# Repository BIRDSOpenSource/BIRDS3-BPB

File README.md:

<p align="center">
<a href="https://lean-sat.org/opensource/" class="button icon calendar">Join Monthly Webinar</a>
</p>

<div align="center">

</div>

# BIRDS3-BPB
The two different designs of the BPB used in the BIRDS3 mission, one with CPLD and one without.

## About the BIRDS3 Program:

The project was led by Kyushu Institute of Technology in Japan and involves students from Sri Lanka, Bhutan, Nepal and Japan.
Satellite Names: NepaliSat-1 (Nepal), Raavana-1 (Sri Lanka) and Ugiusu (Japan)

Stakeholders: Nepal Academy of Science and Technology (NAST) for Nepal, Arthur C Clarke Institute for Modern Technologies (ACCIMT) for Sri Lanka, and Kyushu Institute of Technology (Kyutech) for Japan.

Project duration: 2018-2020

CubeSat: 1U (10x10x10) cm3

Weight: 1.13kg

Launch Date: 17th April 2019

BIRDS-3 has 4 main missions in total; LoRa Demonstration Mission (LDM), Imaging Mission (CAM), Attitude Determination and Control Mission (ADCS) and Software Configurable Backplane Mission (BPB) 

## Organisation structure

## Features

## I like this project, can I help you?
You are welcome 🙂

* Give us a star ⭐
* Watch repository to be notified about updates 👀
* If you will find some errors, report them in Issues 🐞
* Try Birds designs on some real computer and let us know how it worked in Discussions. 💬
* We would greatly appreciate if you would also tell others about this ecosystem, it helps us to improve BIRDS Open Source. Thank you!

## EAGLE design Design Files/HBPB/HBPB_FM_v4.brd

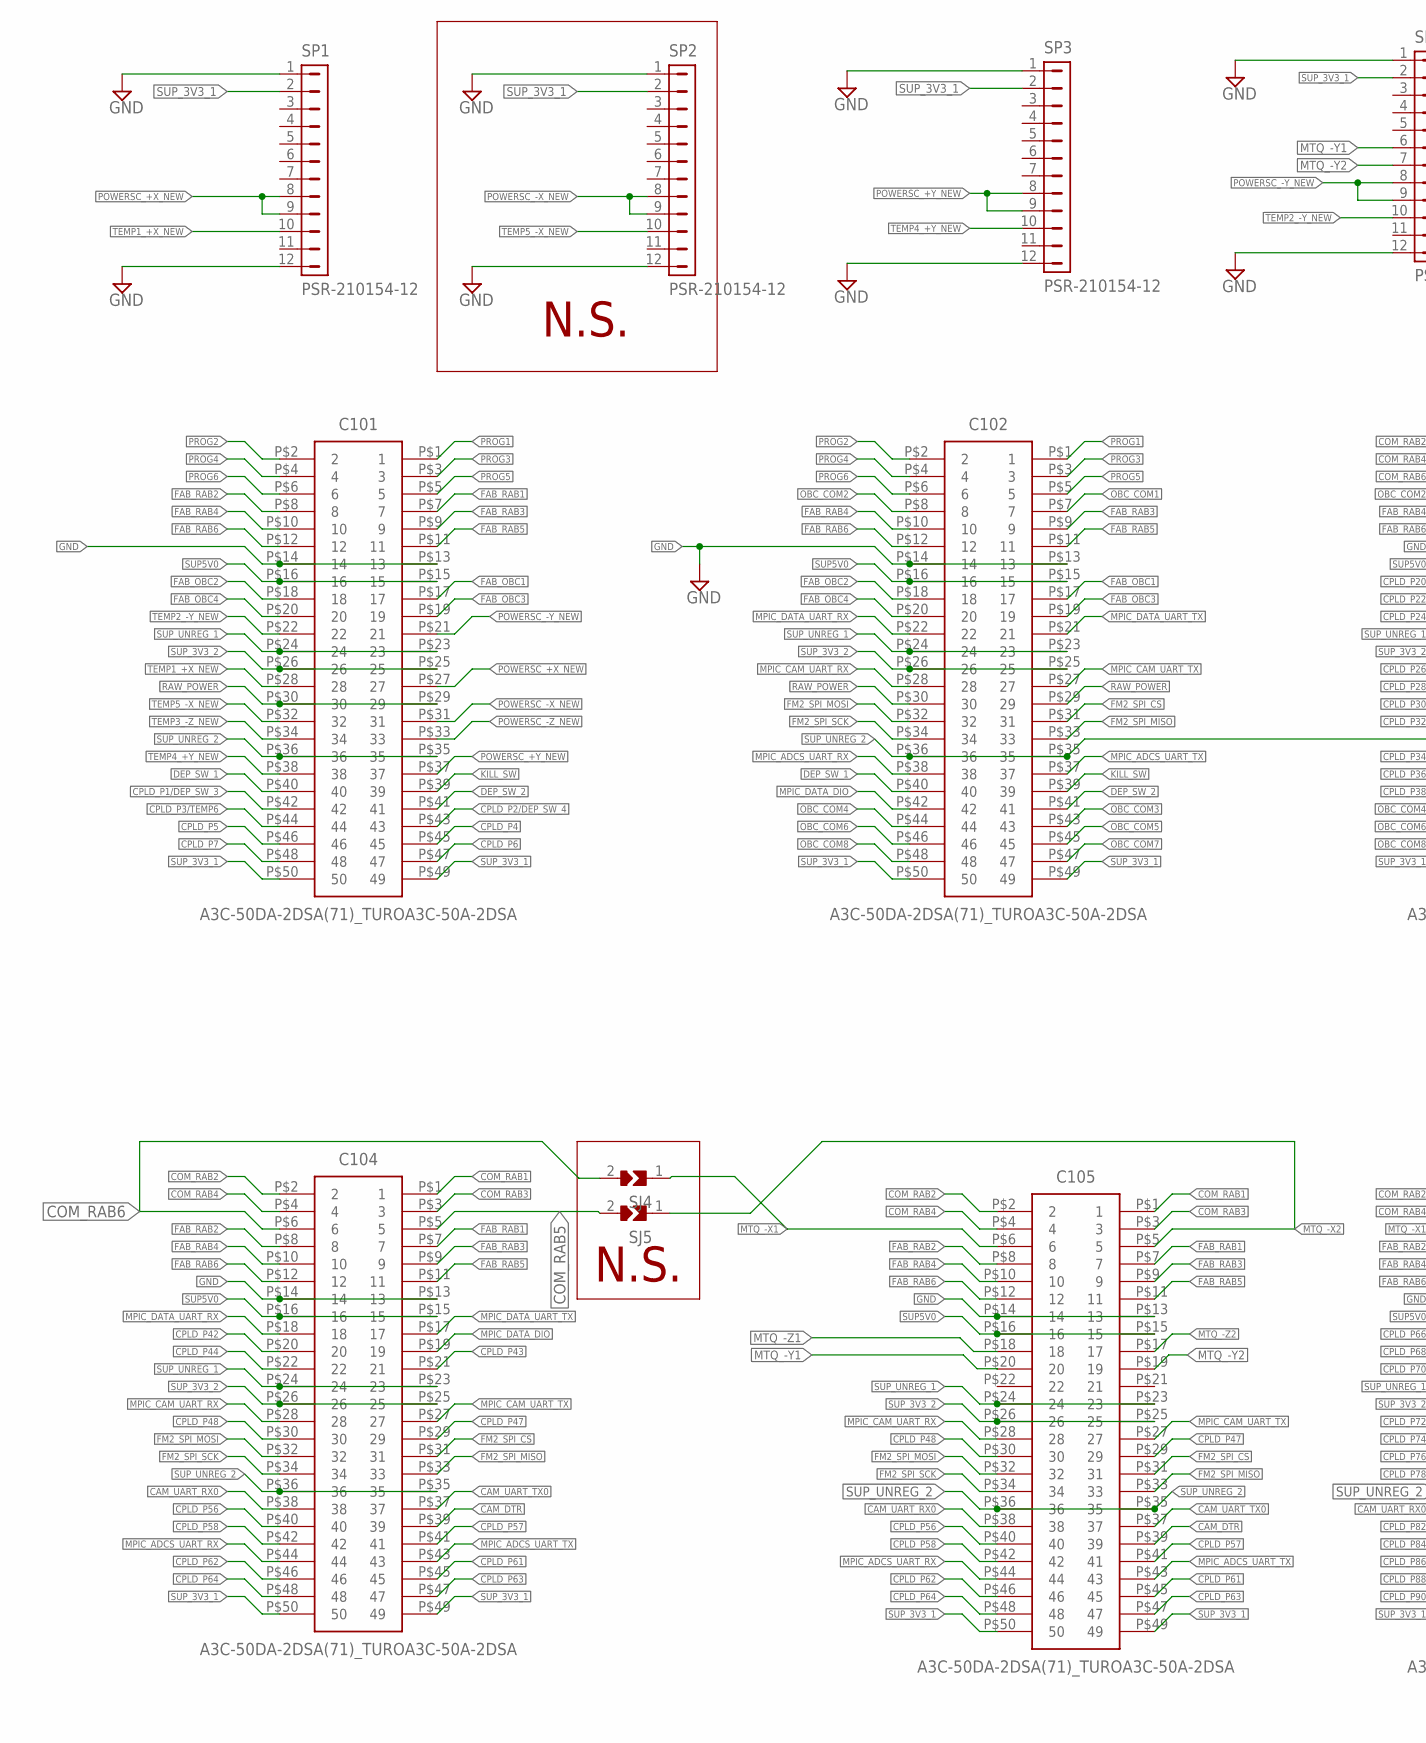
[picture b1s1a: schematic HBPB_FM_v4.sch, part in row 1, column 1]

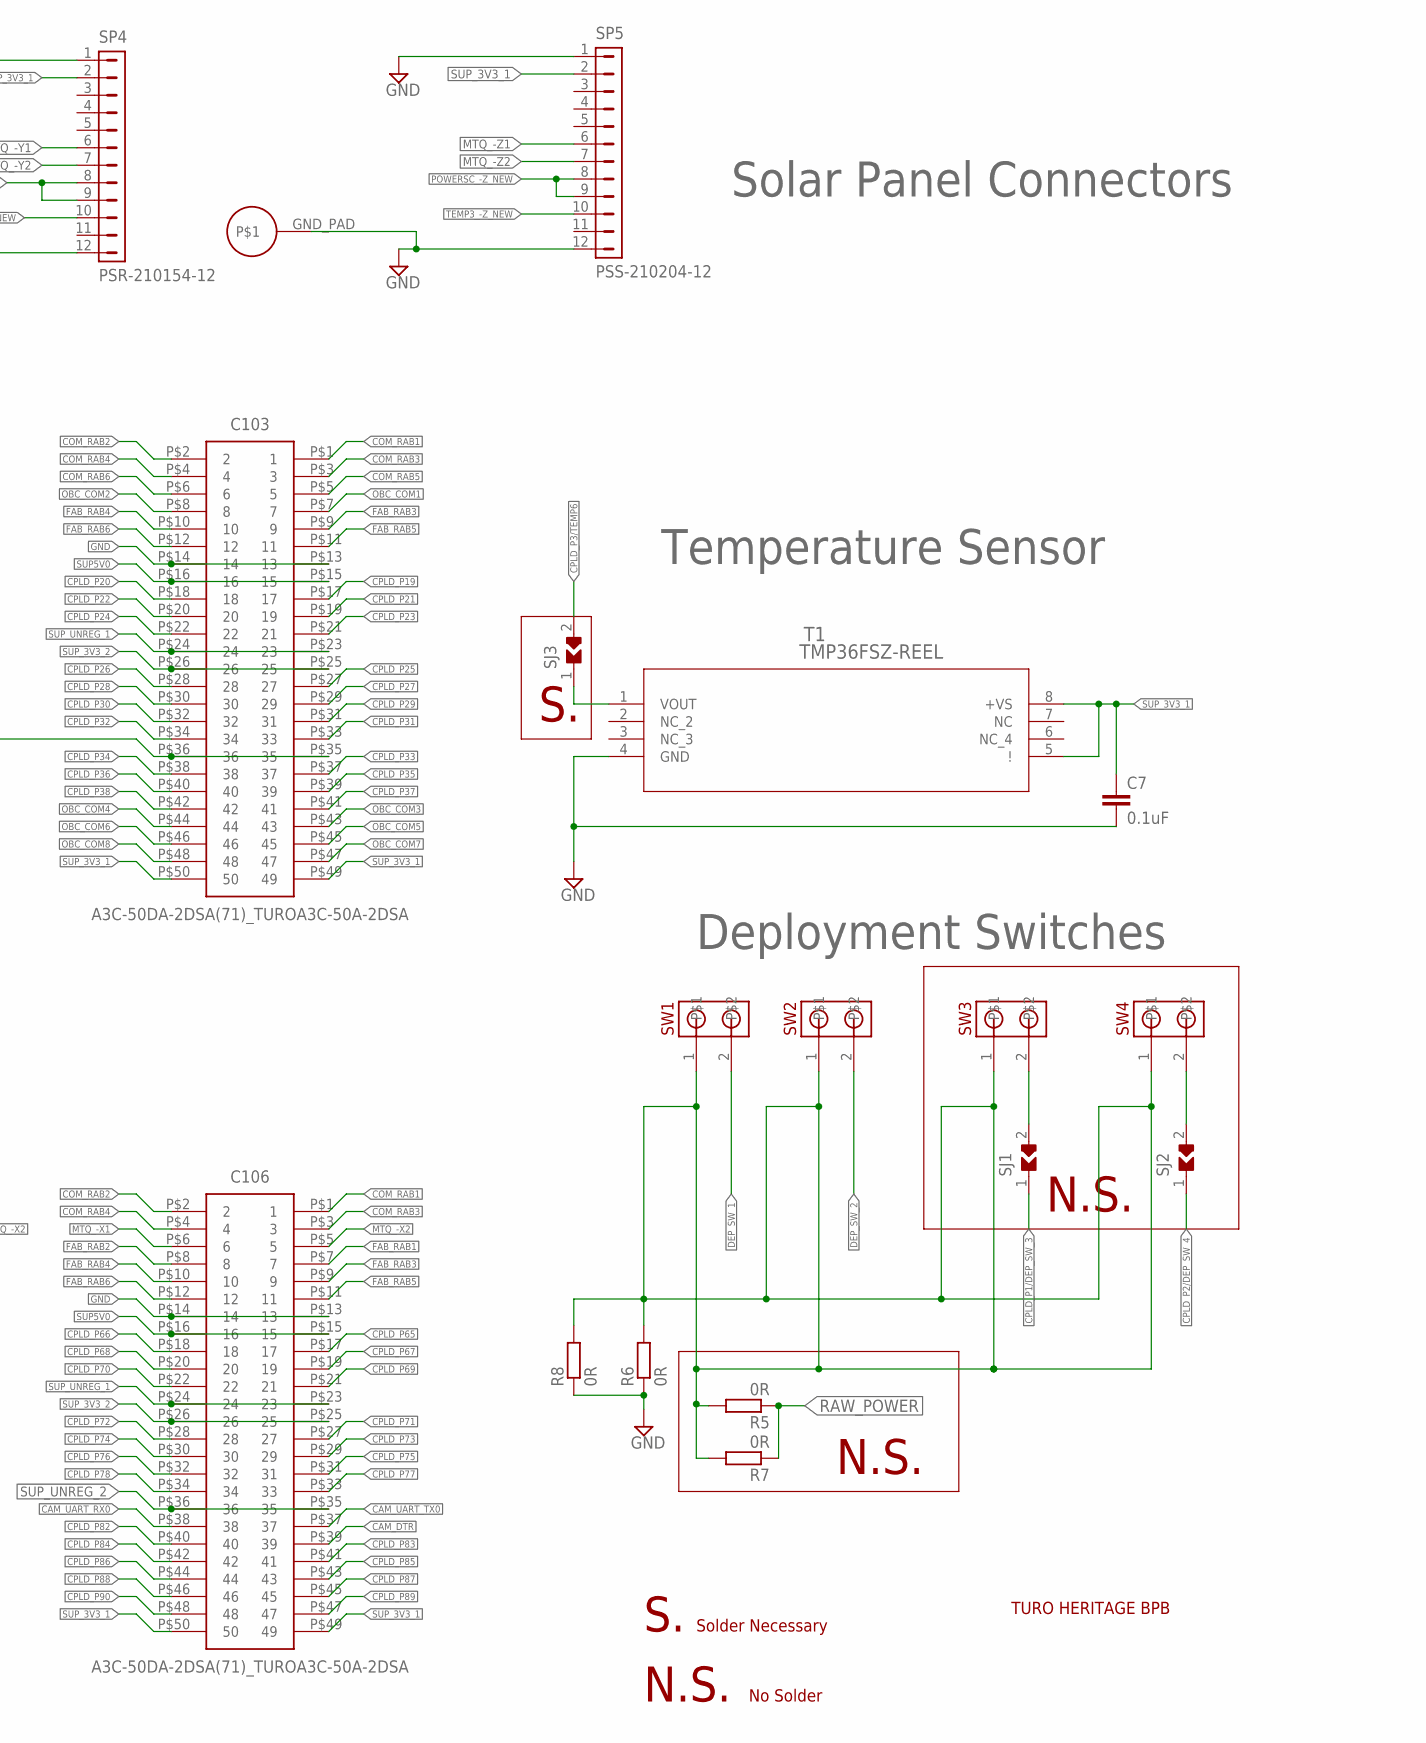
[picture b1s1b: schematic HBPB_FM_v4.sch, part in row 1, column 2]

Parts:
C7: 0.1uF; C0402
C101, C102, C103, C104, C105, C106: A3C-50DA-2DSA(71)_TUROA3C-50A-2DSA; SHDR50W60P200_2X25_5000X400X44_TR
R5, R6, R7, R8: 0R; R3216
SJ1, SJ3, SJ4, SJ5: SJ_BY_TURO; SJ_TURO
SJ2: 0R; SJ_TURO
SP1, SP2, SP3, SP4: PSR-210154-12; PIN1X12/90
SP5: PSS-210204-12; PIN1X12
SW1, SW2, SW3, SW4: MOLEX-CONN-2-0554600272; MOLEX-CONN-2-BIRDS
T1: TMP36FSZ-REEL; R_8
U$1: GND_PAD

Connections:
CAM_DTR: C104.P$39 (39), C105.P$39 (39), C106.P$39 (39)
CAM_UART_RX0: C104.P$38 (38), C105.P$38 (38), C106.P$38 (38)
CAM_UART_TX0: C104.P$37 (37), C105.P$37 (37), C106.P$37 (37)
COM_RAB1: C103.P$1 (1), C104.P$1 (1), C105.P$1 (1), C106.P$1 (1)
COM_RAB2: C103.P$2 (2), C104.P$2 (2), C105.P$2 (2), C106.P$2 (2)
COM_RAB3: C103.P$3 (3), C104.P$3 (3), C105.P$3 (3), C106.P$3 (3)
COM_RAB4: C103.P$4 (4), C104.P$4 (4), C105.P$4 (4), C106.P$4 (4)
COM_RAB5: C103.P$5 (5), C104.P$5 (5), SJ5.2
COM_RAB6: C103.P$6 (6), C104.P$6 (6), SJ4.2
CPLD_P1/DEP_SW_3: C101.P$42 (42), SJ1.1
CPLD_P2/DEP_SW_4: C101.P$43 (43), SJ2.1
CPLD_P3/TEMP6: C101.P$44 (44), SJ3.2
CPLD_P4: C101.P$45 (45)
CPLD_P5: C101.P$46 (46)
CPLD_P6: C101.P$47 (47)
CPLD_P7: C101.P$48 (48)
CPLD_P19: C103.P$17 (17)
CPLD_P20: C103.P$18 (18)
CPLD_P21: C103.P$19 (19)
CPLD_P22: C103.P$20 (20)
CPLD_P23: C103.P$21 (21)
CPLD_P24: C103.P$22 (22)
CPLD_P25: C103.P$27 (27)
CPLD_P26: C103.P$28 (28)
CPLD_P27: C103.P$29 (29)
CPLD_P28: C103.P$30 (30)
CPLD_P29: C103.P$31 (31)
CPLD_P30: C103.P$32 (32)
CPLD_P31: C103.P$33 (33)
CPLD_P32: C103.P$34 (34)
CPLD_P33: C103.P$37 (37)
CPLD_P34: C103.P$38 (38)
CPLD_P35: C103.P$39 (39)
CPLD_P36: C103.P$40 (40)
CPLD_P37: C103.P$41 (41)
CPLD_P38: C103.P$42 (42)
CPLD_P42: C104.P$20 (20)
CPLD_P43: C104.P$21 (21)
CPLD_P44: C104.P$22 (22)
CPLD_P47: C104.P$29 (29), C105.P$29 (29)
CPLD_P48: C104.P$30 (30), C105.P$30 (30)
CPLD_P56: C104.P$40 (40), C105.P$40 (40)
CPLD_P57: C104.P$41 (41), C105.P$41 (41)
CPLD_P58: C104.P$42 (42), C105.P$42 (42)
CPLD_P61: C104.P$45 (45), C105.P$45 (45)
CPLD_P62: C104.P$46 (46), C105.P$46 (46)
CPLD_P63: C104.P$47 (47), C105.P$47 (47)
CPLD_P64: C104.P$48 (48), C105.P$48 (48)
CPLD_P65: C106.P$17 (17)
CPLD_P66: C106.P$18 (18)
CPLD_P67: C106.P$19 (19)
CPLD_P68: C106.P$20 (20)
CPLD_P69: C106.P$21 (21)
CPLD_P70: C106.P$22 (22)
CPLD_P71: C106.P$27 (27)
CPLD_P72: C106.P$28 (28)
CPLD_P73: C106.P$29 (29)
CPLD_P74: C106.P$30 (30)
CPLD_P75: C106.P$31 (31)
CPLD_P76: C106.P$32 (32)
CPLD_P77: C106.P$33 (33)
CPLD_P78: C106.P$34 (34)
CPLD_P82: C106.P$40 (40)
CPLD_P83: C106.P$41 (41)
CPLD_P84: C106.P$42 (42)
CPLD_P85: C106.P$43 (43)
CPLD_P86: C106.P$44 (44)
CPLD_P87: C106.P$45 (45)
CPLD_P88: C106.P$46 (46)
CPLD_P89: C106.P$47 (47)
CPLD_P90: C106.P$48 (48)
DEP_SW_1: C101.P$40 (40), C102.P$40 (40), SW1.2
DEP_SW_2: C101.P$41 (41), C102.P$41 (41), SW2.2
DEP_SW_POWER: R5.2, R6.2, R7.2, R8.2, SW1.1, SW2.1, SW3.1, SW4.1
FAB_OBC1: C101.P$17 (17), C102.P$17 (17)
FAB_OBC2: C101.P$18 (18), C102.P$18 (18)
FAB_OBC3: C101.P$19 (19), C102.P$19 (19)
FAB_OBC4: C101.P$20 (20), C102.P$20 (20)
FAB_RAB1: C101.P$7 (7), C104.P$7 (7), C105.P$7 (7), C106.P$7 (7)
FAB_RAB2: C101.P$8 (8), C104.P$8 (8), C105.P$8 (8), C106.P$8 (8)
FAB_RAB3: C101.P$9 (9), C102.P$9 (9), C103.P$9 (9), C104.P$9 (9), C105.P$9 (9), C106.P$9 (9)
FAB_RAB4: C101.P$10 (10), C102.P$10 (10), C103.P$10 (10), C104.P$10 (10), C105.P$10 (10), C106.P$10 (10)
FAB_RAB5: C101.P$11 (11), C102.P$11 (11), C103.P$11 (11), C104.P$11 (11), C105.P$11 (11), C106.P$11 (11)
FAB_RAB6: C101.P$12 (12), C102.P$12 (12), C103.P$12 (12), C104.P$12 (12), C105.P$12 (12), C106.P$12 (12)
FM2_SPI_CS: C102.P$31 (31), C104.P$31 (31), C105.P$31 (31)
FM2_SPI_MISO: C102.P$33 (33), C104.P$33 (33), C105.P$33 (33)
FM2_SPI_MOSI: C102.P$32 (32), C104.P$32 (32), C105.P$32 (32)
FM2_SPI_SCK: C102.P$34 (34), C104.P$34 (34), C105.P$34 (34)
GND: C7.2, C101.P$13 (13), C101.P$14 (14), C102.P$13 (13), C102.P$14 (14), C103.P$13 (13), C103.P$14 (14), C104.P$13 (13), C104.P$14 (14), C105.P$13 (13), C105.P$14 (14), C106.P$13 (13), C106.P$14 (14), R6.1, R8.1, SP1.1, SP1.12, SP2.1, SP2.12, SP3.1, SP3.12, SP4.1, SP4.12, SP5.1, SP5.12, T1.4 (GND), U$1.GND_PAD
KILL_SW: C101.P$39 (39), C102.P$39 (39)
MPIC_ADCS_UART_RX: C102.P$38 (38), C104.P$44 (44), C105.P$44 (44)
MPIC_ADCS_UART_TX: C102.P$37 (37), C104.P$43 (43), C105.P$43 (43)
MPIC_CAM_UART_RX: C102.P$28 (28), C104.P$28 (28), C105.P$28 (28)
MPIC_CAM_UART_TX: C102.P$27 (27), C104.P$27 (27), C105.P$27 (27)
MPIC_DATA_DIO: C102.P$42 (42), C104.P$19 (19)
MPIC_DATA_UART_RX: C102.P$22 (22), C104.P$18 (18)
MPIC_DATA_UART_TX: C102.P$21 (21), C104.P$17 (17)
MTQ_-X1: C105.P$6 (6), C106.P$6 (6), SJ4.1
MTQ_-X2: C105.P$5 (5), C106.P$5 (5), SJ5.1
MTQ_-Y1: C105.P$20 (20), SP4.6
MTQ_-Y2: C105.P$19 (19), SP4.7
MTQ_-Z1: C105.P$18 (18), SP5.6
MTQ_-Z2: C105.P$17 (17), SP5.7
unnamed: SJ2.2, SW4.2
unnamed: SJ1.2, SW3.2
unnamed: SJ3.1, T1.1 (VOUT)
OBC_COM1: C102.P$7 (7), C103.P$7 (7)
OBC_COM2: C102.P$8 (8), C103.P$8 (8)
OBC_COM3: C102.P$43 (43), C103.P$43 (43)
OBC_COM4: C102.P$44 (44), C103.P$44 (44)
OBC_COM5: C102.P$45 (45), C103.P$45 (45)
OBC_COM6: C102.P$46 (46), C103.P$46 (46)
OBC_COM7: C102.P$47 (47), C103.P$47 (47)
OBC_COM8: C102.P$48 (48), C103.P$48 (48)
POWERSC_+X_NEW: C101.P$27 (27), SP1.8, SP1.9
POWERSC_+Y_NEW: C101.P$37 (37), SP3.8, SP3.9
POWERSC_-X_NEW: C101.P$31 (31), SP2.8, SP2.9
POWERSC_-Y_NEW: C101.P$21 (21), SP4.8, SP4.9
POWERSC_-Z_NEW: C101.P$33 (33), SP5.8, SP5.9
PROG1: C101.P$1 (1), C102.P$1 (1)
PROG2: C101.P$2 (2), C102.P$2 (2)
PROG3: C101.P$3 (3), C102.P$3 (3)
PROG4: C101.P$4 (4), C102.P$4 (4)
PROG5: C101.P$5 (5), C102.P$5 (5)
PROG6: C101.P$6 (6), C102.P$6 (6)
RAW_POWER: C101.P$29 (29), C101.P$30 (30), C102.P$29 (29), C102.P$30 (30), R5.1, R7.1
SUP5V0: C101.P$15 (15), C101.P$16 (16), C102.P$15 (15), C102.P$16 (16), C103.P$15 (15), C103.P$16 (16), C104.P$15 (15), C104.P$16 (16), C105.P$15 (15), C105.P$16 (16), C106.P$15 (15), C106.P$16 (16)
SUP_3V3_1: C7.1, C101.P$49 (49), C101.P$50 (50), C102.P$49 (49), C102.P$50 (50), C103.P$49 (49), C103.P$50 (50), C104.P$49 (49), C104.P$50 (50), C105.P$49 (49), C105.P$50 (50), C106.P$49 (49), C106.P$50 (50), SP1.2, SP2.2, SP3.2, SP4.2, SP5.2, T1.5 (!), T1.8 (+VS)
SUP_3V3_2: C101.P$25 (25), C101.P$26 (26), C102.P$25 (25), C102.P$26 (26), C103.P$25 (25), C103.P$26 (26), C104.P$25 (25), C104.P$26 (26), C105.P$25 (25), C105.P$26 (26), C106.P$25 (25), C106.P$26 (26)
SUP_UNREG_1: C101.P$23 (23), C101.P$24 (24), C102.P$23 (23), C102.P$24 (24), C103.P$23 (23), C103.P$24 (24), C104.P$23 (23), C104.P$24 (24), C105.P$23 (23), C105.P$24 (24), C106.P$23 (23), C106.P$24 (24)
SUP_UNREG_2: C101.P$35 (35), C101.P$36 (36), C102.P$35 (35), C102.P$36 (36), C103.P$35 (35), C103.P$36 (36), C104.P$35 (35), C104.P$36 (36), C105.P$35 (35), C105.P$36 (36), C106.P$35 (35), C106.P$36 (36)
TEMP1_+X_NEW: C101.P$28 (28), SP1.10
TEMP2_-Y_NEW: C101.P$22 (22), SP4.10
TEMP3_-Z_NEW: C101.P$34 (34), SP5.10
TEMP4_+Y_NEW: C101.P$38 (38), SP3.10
TEMP5_-X_NEW: C101.P$32 (32), SP2.10

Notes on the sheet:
Temperature Sensor
Deployment Switches
Solar Panel Connectors
TURO HERITAGE BPB
N.S.
Solder Necessary
No Solder

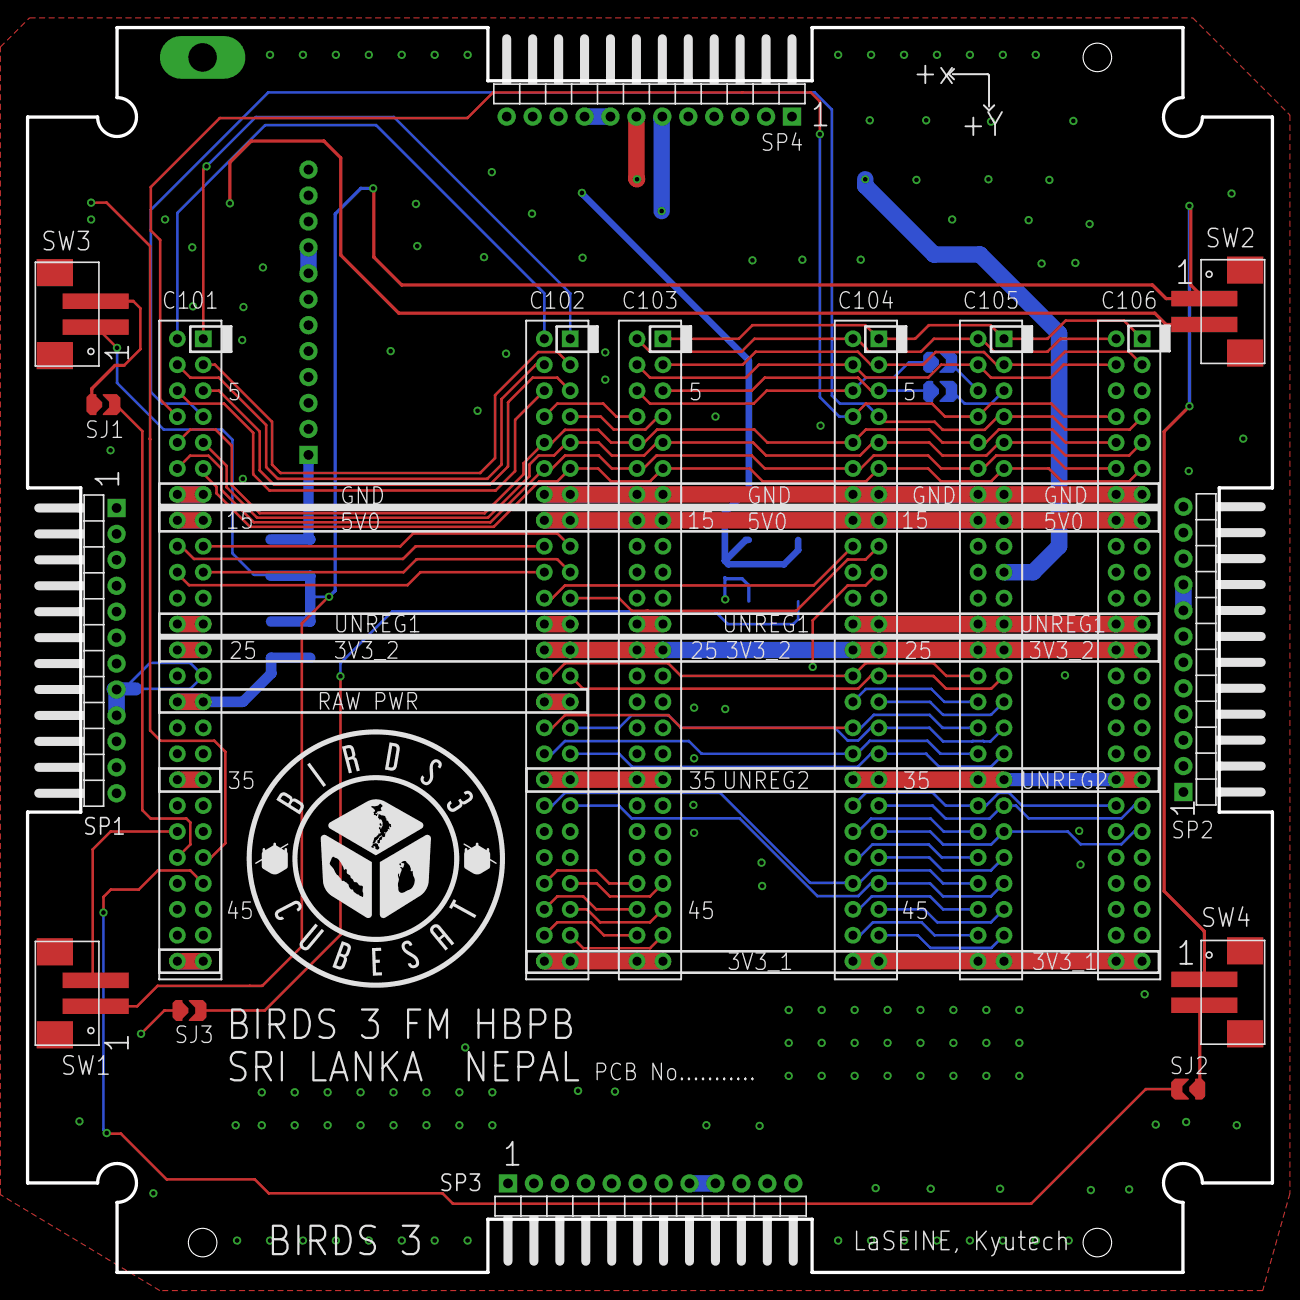
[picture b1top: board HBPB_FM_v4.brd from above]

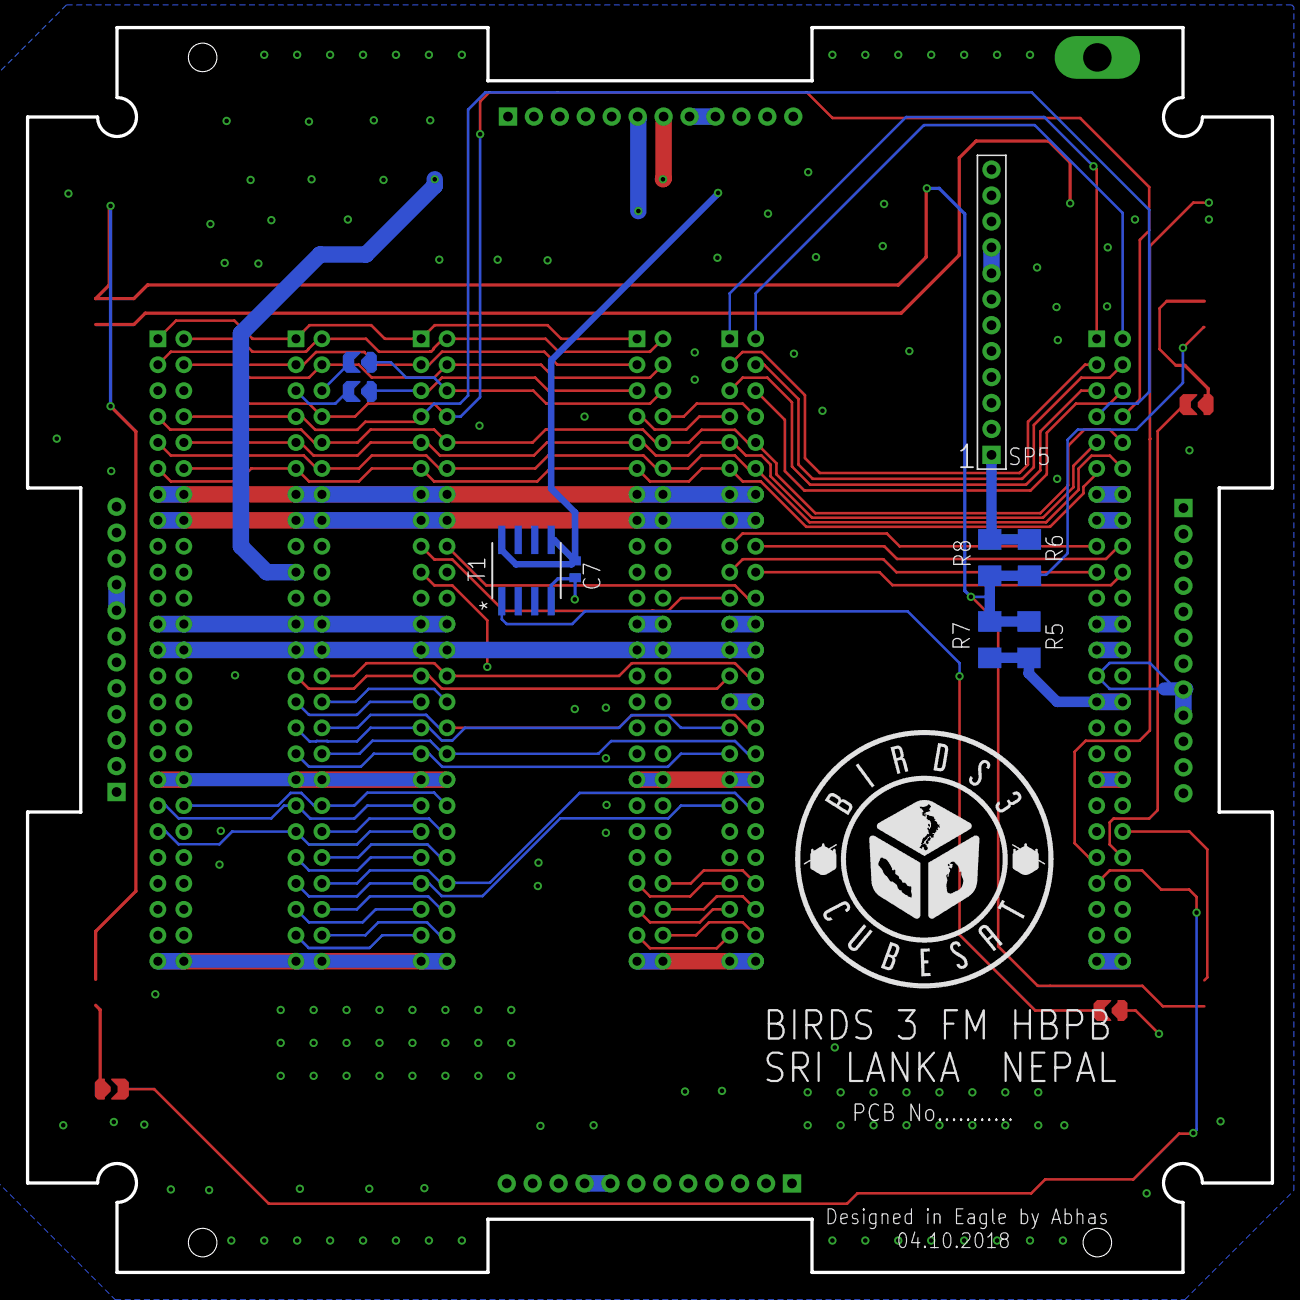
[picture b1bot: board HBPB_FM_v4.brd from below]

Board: 6 copper layers, 96.0 x 96.0 mm, 27 parts (9 on the bottom side), 86 nets.

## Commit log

2021-09-08 Initial file upload
    Done by Kevin
2021-10-20 Update LICENSE
